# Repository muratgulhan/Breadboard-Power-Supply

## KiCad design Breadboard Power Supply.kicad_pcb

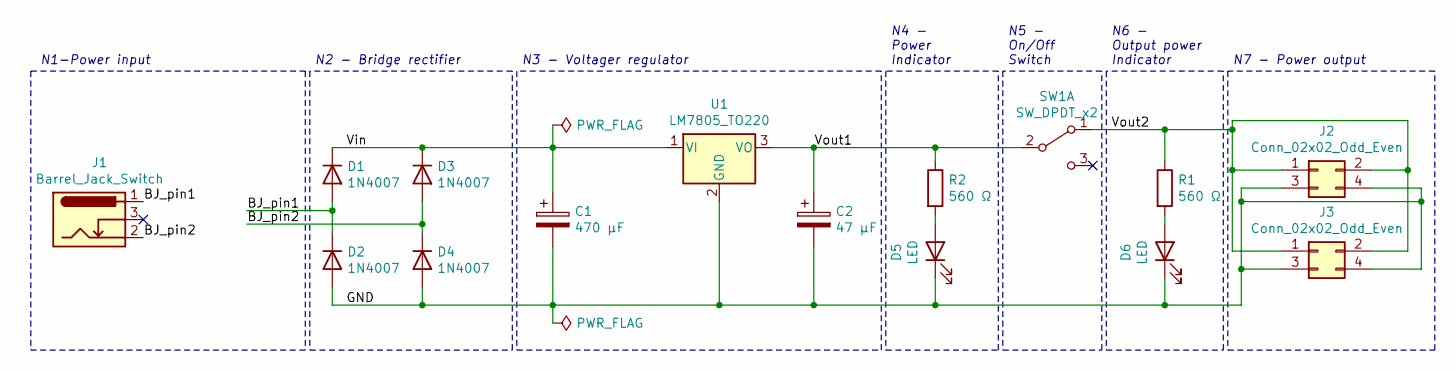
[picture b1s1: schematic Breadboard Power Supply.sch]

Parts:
C1: 470 μF; CP_Radial_D10.0mm_P5.00mm
C2: 47 μF; CP_Radial_D6.3mm_P2.50mm
D1, D2, D3, D4: 1N4007; D_DO-41_SOD81_P10.16mm_Horizontal
D5, D6: LED; LED_D5.0mm
J1: Barrel_Jack_Switch; BarrelJack_CUI_PJ-102AH_Horizontal
J2, J3: Conn_02x02_Odd_Even; PinHeader_2x02_P2.54mm_Vertical
R1, R2: 560 Ω; R_Axial_DIN0207_L6.3mm_D2.5mm_P7.62mm_Horizontal
SW1: SW_DPDT_x2; Switch_Slide_11.6x4mm_EG1218
U1: LM7805_TO220; TO-220-3_Vertical

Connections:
/BJ_pin1: D1.2 (A), D2.1 (K), J1.1
/BJ_pin2: D3.2 (A), D4.1 (K), J1.2
/GND: C1.2, C2.2, D2.2 (A), D4.2 (A), D5.1 (K), D6.1 (K), J2.3, J2.4, J3.3, J3.4, U1.2 (GND)
/Vin: C1.1, D1.1 (K), D3.1 (K), U1.1 (VI)
/Vout1: C2.1, R2.1, SW1.2 (B), U1.3 (VO)
/Vout2: J2.1, J2.2, J3.1, J3.2, R1.1, SW1.1 (A)
unnamed: D5.2 (A), R2.2
unnamed: D6.2 (A), R1.2

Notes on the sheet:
N1-Power input
N2 - Bridge rectifier
N3 - Voltager regulator
N4 - Power Indicator
N5 - On/Off Switch
N6 - Output power Indicator
N7 - Power output

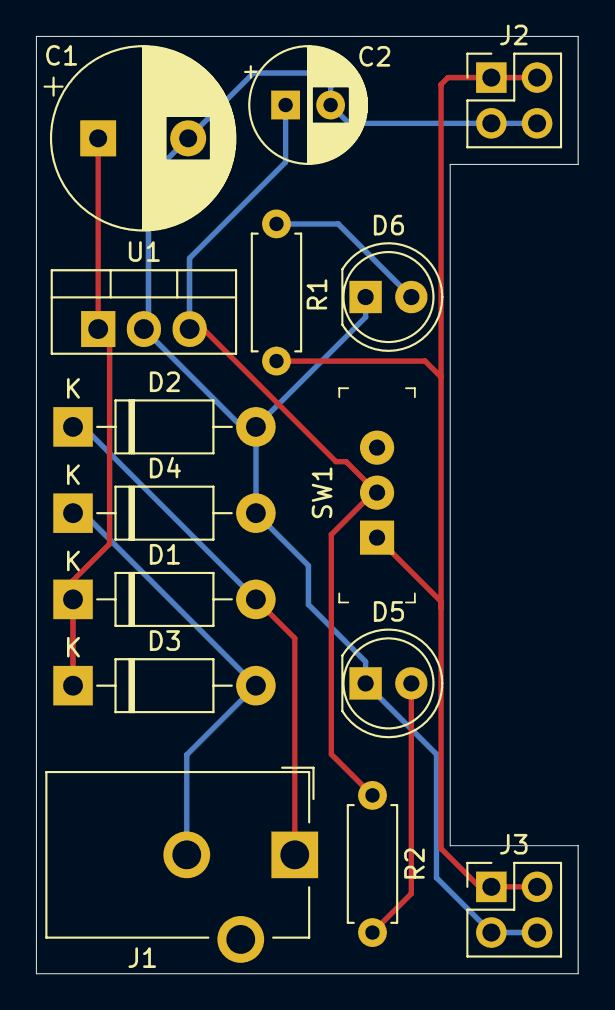
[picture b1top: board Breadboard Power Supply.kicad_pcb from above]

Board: 2 copper layers, 30.1 x 52.1 mm, 15 parts (0 on the bottom side), 8 nets.

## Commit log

2021-08-31 101. video bitti
2021-09-01 102. video yarıda kaldı
2021-09-01 102 bitti
2021-09-01 103. video ortada kaldı
2021-09-02 104. video tamamlandı
2021-09-05 project finished
